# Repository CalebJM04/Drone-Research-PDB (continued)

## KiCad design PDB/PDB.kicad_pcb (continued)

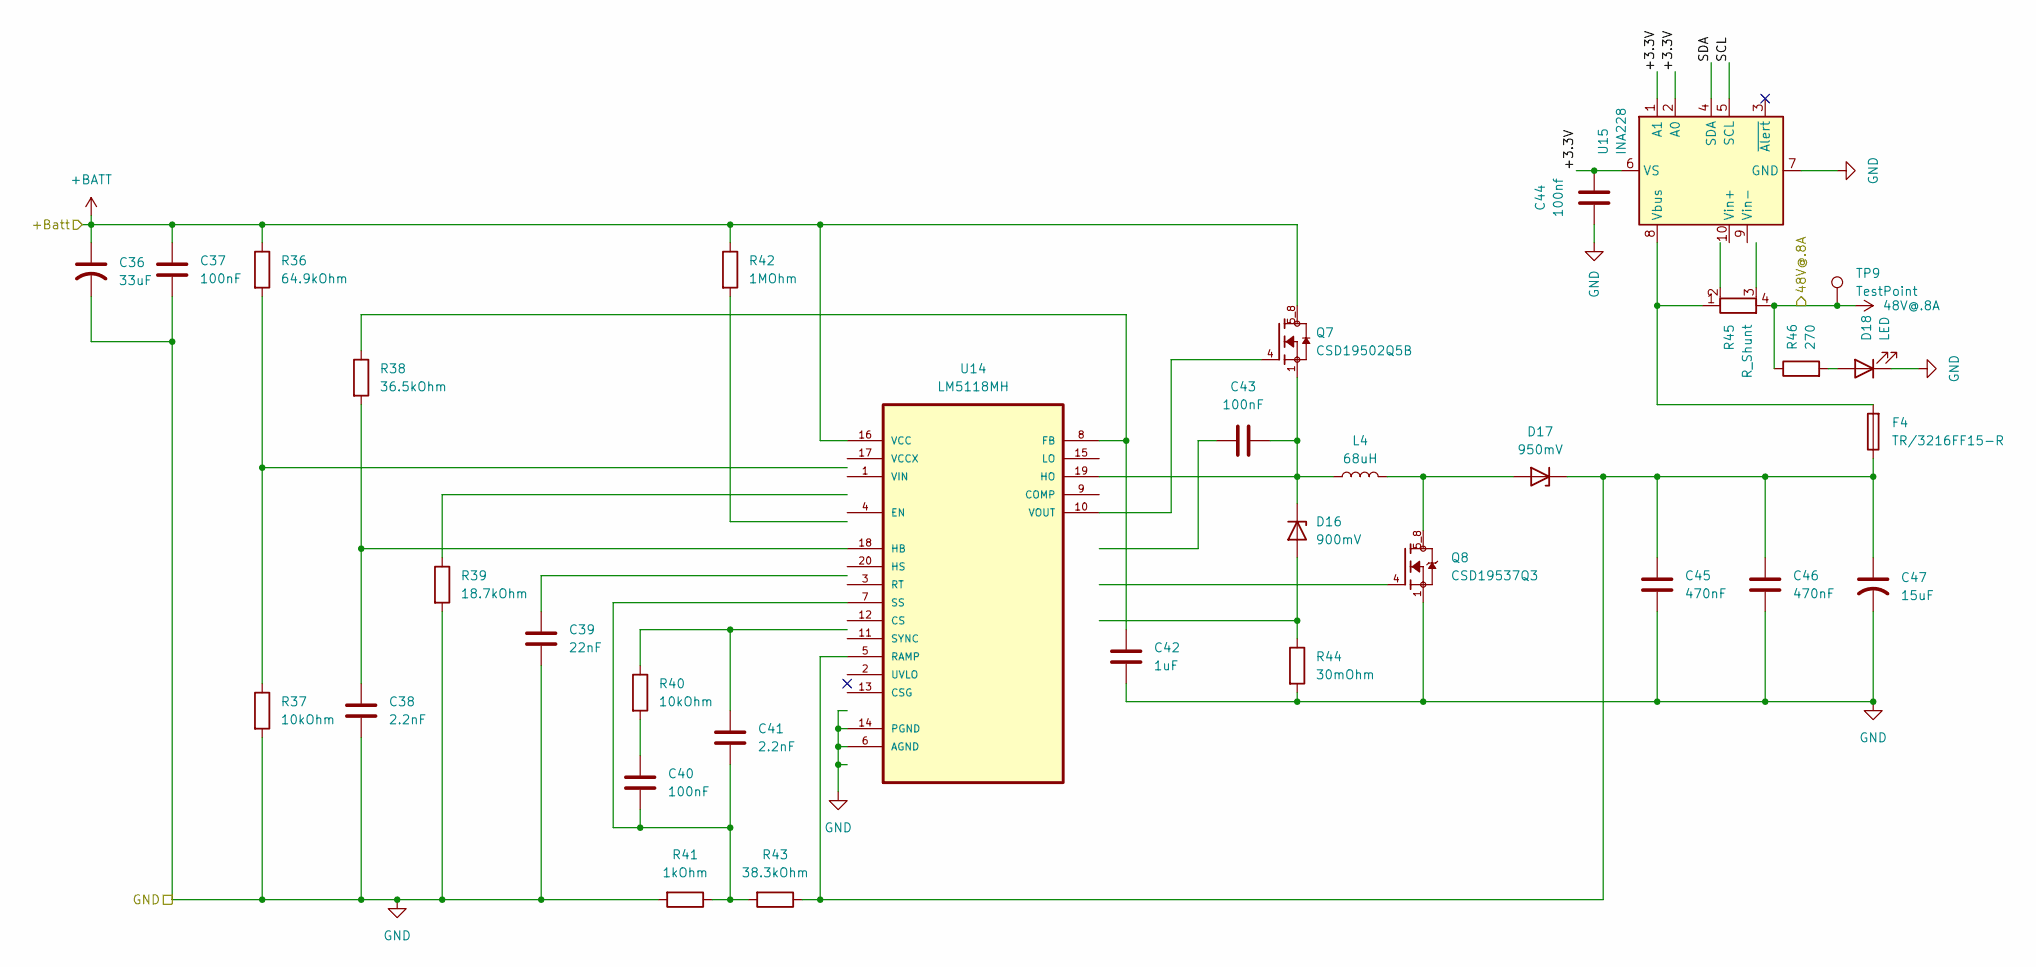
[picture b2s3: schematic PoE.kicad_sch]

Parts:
C36: 33uF; C_0603_1608Metric
C37, C40, C43: 100nF; C_0603_1608Metric
C38, C41: 2.2nF; C_0603_1608Metric
C39: 22nF; C_0603_1608Metric
C42: 1uF; C_0603_1608Metric
C44: 100nf; C_0603_1608Metric
C45, C46: 470nF; C_0603_1608Metric
C47: 15uF; C_0603_1608Metric
D16: 900mV; D_SOD-523
D17: 950mV; D_SOD-523
D18: LED; LED_0805_2012Metric
F4: TR/3216FF15-R; Fuse_1206_3216Metric
L4: 68uH; L_1206_3216Metric
Q7: CSD19502Q5B; TRANS_CSD19502Q5B; PARTREV May 2017; DigiKey_Part_Number 296-37194-1-ND
Q8: CSD19537Q3; TRANS_CSD19537Q3; PARTREV A; DigiKey_Part_Number 296-44351-1-ND
R36: 64.9kOhm; R_0603_1608Metric
R37, R40: 10kOhm; R_0603_1608Metric
R38: 36.5kOhm; R_0603_1608Metric
R39: 18.7kOhm; R_0603_1608Metric
R41: 1kOhm; R_0603_1608Metric
R42: 1MOhm; R_0603_1608Metric
R43: 38.3kOhm; R_0603_1608Metric
R44: 30mOhm; R_0603_1608Metric
R45: R_Shunt; R_Shunt_Vishay_WSK2512_6332Metric_T2.66mm
R46: 270; R_1206_3216Metric_Pad1.30x1.75mm_HandSolder
TP9: TestPoint; TestPoint_Pad_D2.0mm
U14: LM5118MH; SOP65P640X110-21N; MPN LM5118MH; DigiKey_Part_Number LM5118MH/NOPB-ND
U15: INA228; TSSOP-10_3x3mm_P0.5mm

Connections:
48V@.8A: R45.4, R46.1, TP9.1 (1_1)
+BATT: C36.1, C37.1, Q7.5_8, R36.1, R42.1, U14.16 (VCC); also elsewhere on the board
/48V@.8A/+3.3V: C44.2, U15.1 (A1), U15.2 (A0), U15.6 (VS)
/48V@.8A/SCL: U15.5 (SCL)
/48V@.8A/SDA: U15.4 (SDA)
GND: C36.2, C37.2, C38.2, C39.2, C42.2, C44.1, C45.2, C46.2, C47.2, D18.1 (K), Q8.1, Q8.2, Q8.3, R37.2, R39.2, R41.2, R44.2, U14.6 (AGND), U14.14 (PGND), U15.7 (GND); also elsewhere on the board
unnamed: C40.1, R40.2
unnamed: C41.1, R40.1
unnamed: D16.2 (A), R44.1
unnamed: C43.1, D16.1 (K), L4.1, Q7.1, Q7.2, Q7.3, U14.19 (HO)
unnamed: D17.2 (A), L4.2, Q8.5_8
unnamed: C45.1, C46.1, C47.1, D17.1 (K), F4.1, R43.1, U14.5 (RAMP)
unnamed: D18.2 (A), R46.2
unnamed: R36.2, R37.1
unnamed: C42.1, R38.1, U14.8 (FB)
unnamed: C38.1, R38.2, U14.18 (HB)
unnamed: C40.2, C41.2, R41.1, R43.2, U14.7 (SS)
unnamed: Q7.4, U14.10 (VOUT)
unnamed: F4.2, R45.1, U15.8 (Vbus)

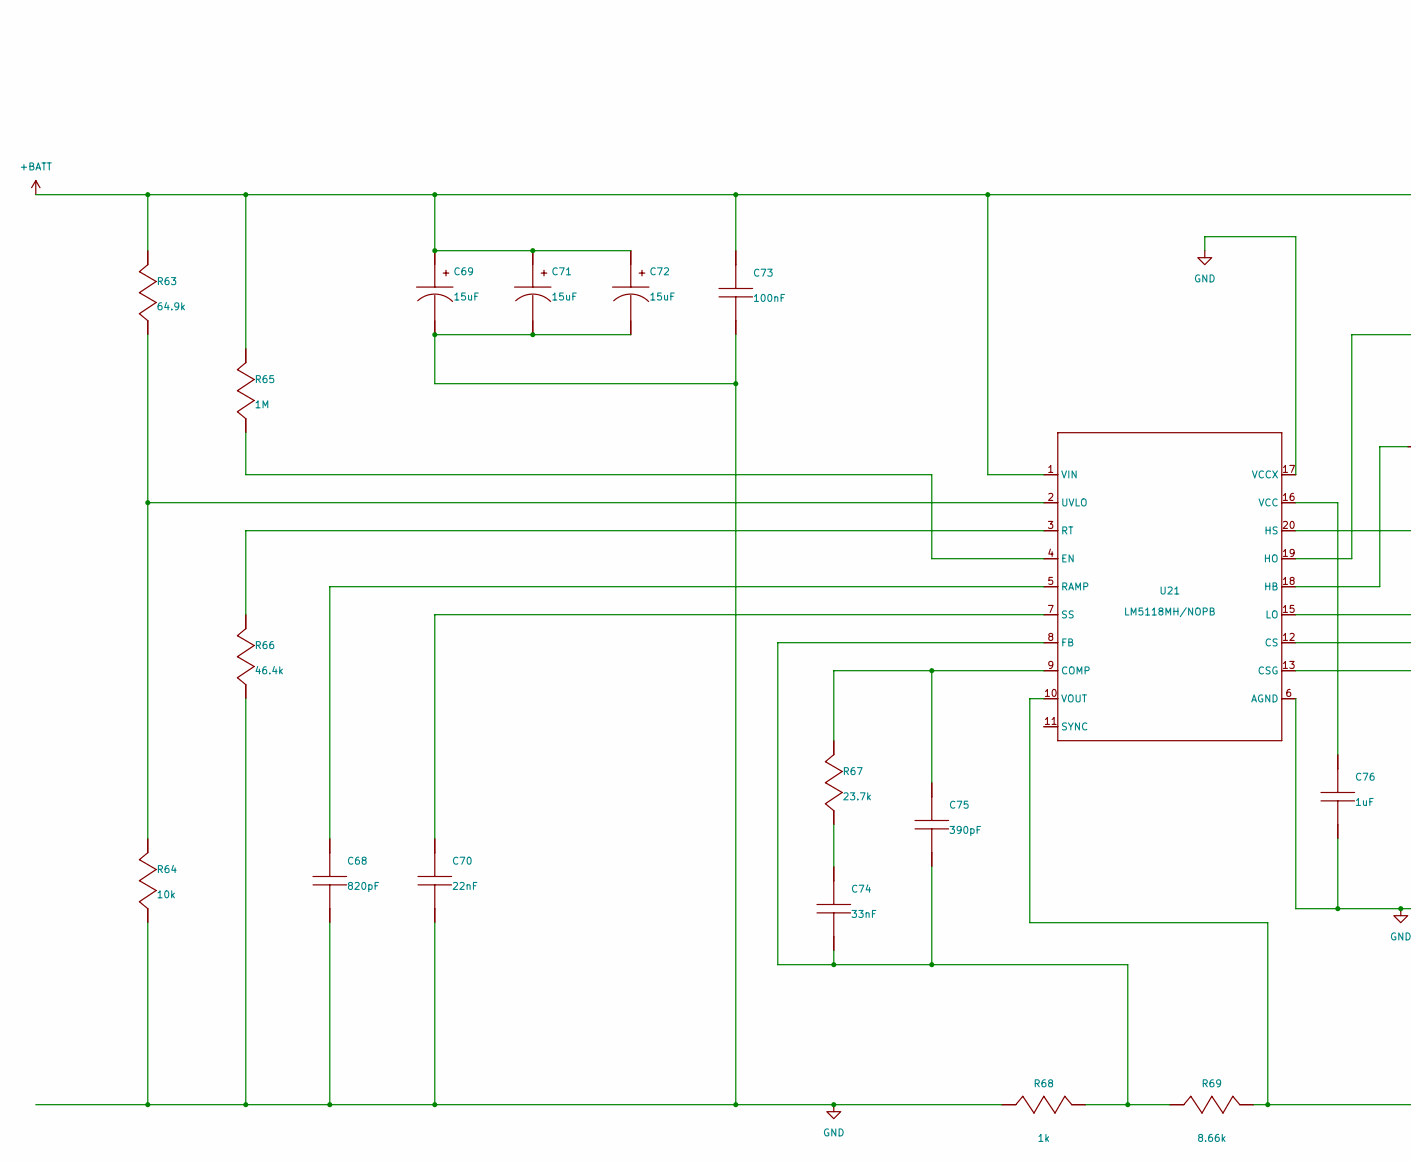
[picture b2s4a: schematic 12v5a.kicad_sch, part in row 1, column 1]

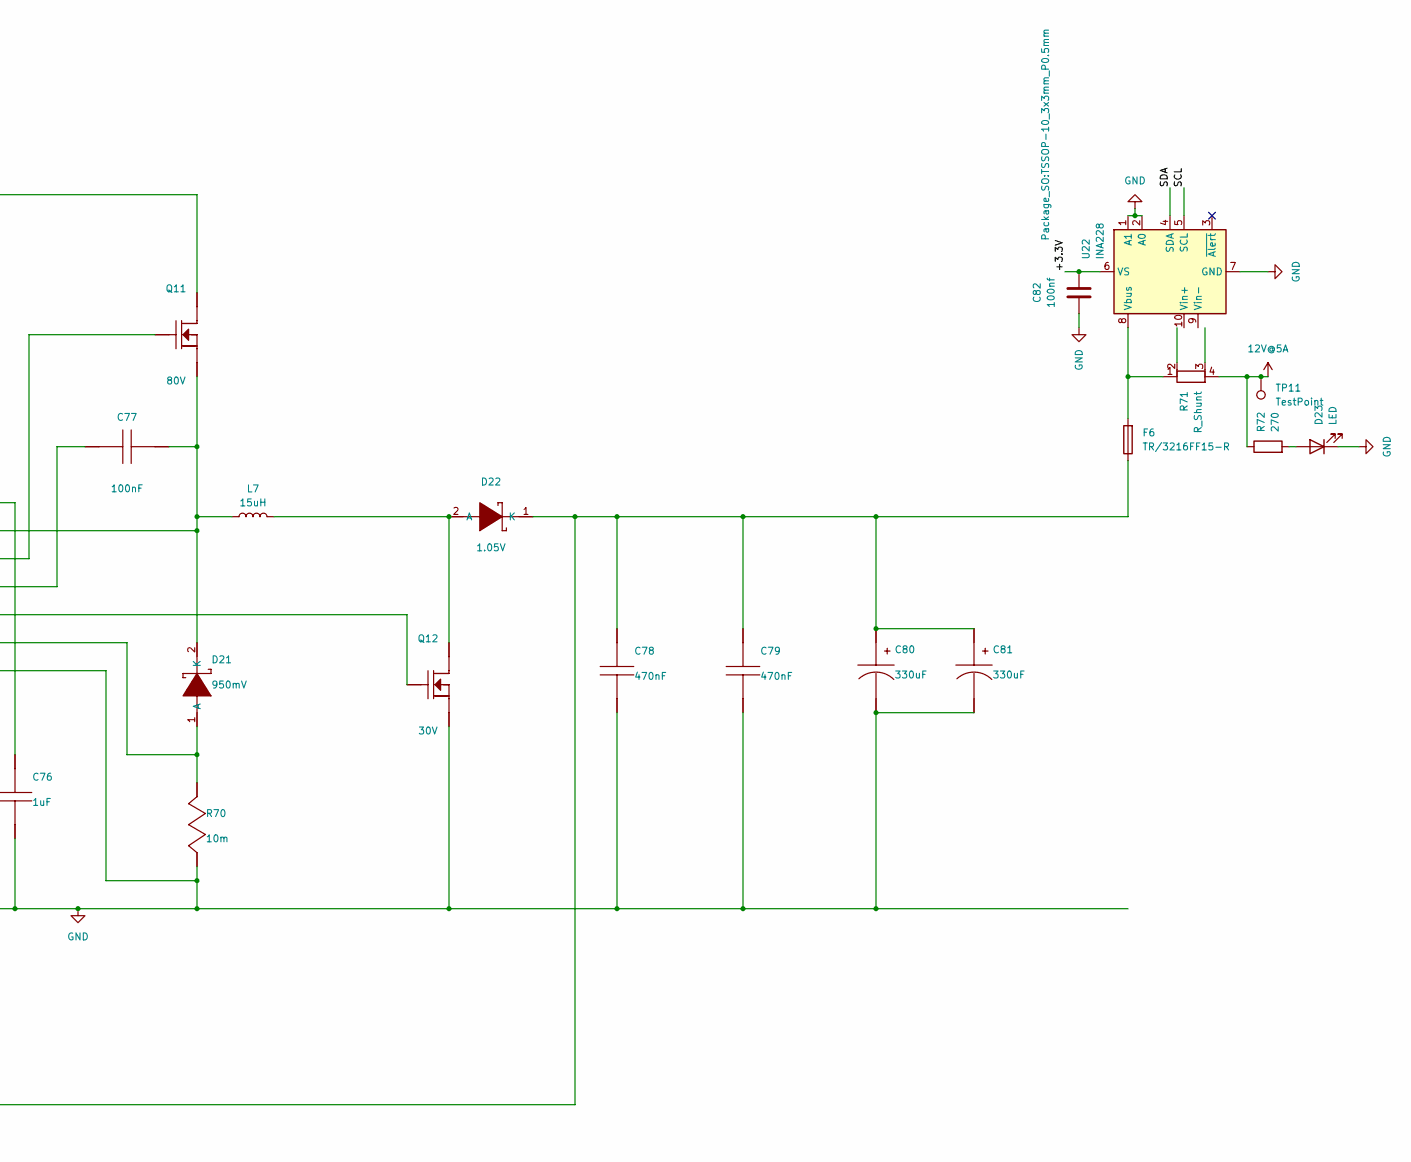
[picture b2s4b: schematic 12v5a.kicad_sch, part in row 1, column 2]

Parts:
C68: CL05C821JB5NNNC; C_0603_1608Metric; MANUFACTURER PART NUMBER CL05C821JB5NNNC
C69, C71, C72: 100SXV15M; C_0603_1608Metric; MANUFACTURER PART NUMBER 100SXV15M
C70: C2012C0G1H223K125AA; C_0603_1608Metric; MANUFACTURER PART NUMBER C2012C0G1H223K125AA
C73: C2012X7R2A104K125AA; C_0603_1608Metric; MANUFACTURER PART NUMBER C2012X7R2A104K125AA
C74: CGA4J2C0G1H333J125AA; C_0603_1608Metric; MANUFACTURER PART NUMBER CGA4J2C0G1H333J125AA
C75: GRM1555C1H391JA01J; C_0603_1608Metric; MANUFACTURER PART NUMBER GRM1555C1H391JA01J
C76: C1005X5R1E105K050BC; C_0603_1608Metric; MANUFACTURER PART NUMBER C1005X5R1E105K050BC
C77: 08053C104JAZ2A; C_0603_1608Metric; MANUFACTURER PART NUMBER 08053C104JAZ2A
C78, C79: C1005X6S1C474K050BC; C_0603_1608Metric; MANUFACTURER PART NUMBER C1005X6S1C474K050BC
C80, C81: EEHZC1E331P; C_0603_1608Metric; MANUFACTURER PART NUMBER EEHZC1E331P
C82: 100nf; C_0603_1608Metric
D21: SBRD10200TR; TO-252-2_TabPin1; MANUFACTURER PART NUMBER SBRD10200TR
D22: SB20150TR; D_5W_P10.16mm_Horizontal; MANUFACTURER PART NUMBER SB20150TR
D23: LED; LED_0805_2012Metric
F6: TR/3216FF15-R; Fuse_1206_3216Metric
L7: 15uH; L_1206_3216Metric
Q11: CSD19502Q5B; MANUFACTURER PART NUMBER CSD19502Q5B
Q12: CSD17578Q3A; CSD19502Q5B; MANUFACTURER PART NUMBER CSD17578Q3A
R63: CRCW040264K9FKED; R_0603_1608Metric; MANUFACTURER PART NUMBER CRCW040264K9FKED
R64: RC0201FR-0710KL; R_0603_1608Metric; MANUFACTURER PART NUMBER RC0201FR-0710KL
R65: CRCW04021M00FKED; R_0603_1608Metric; MANUFACTURER PART NUMBER CRCW04021M00FKED
R66: CRCW040246K4FKED; R_0603_1608Metric; MANUFACTURER PART NUMBER CRCW040246K4FKED
R67: RC0201FR-0723K7L; R_0603_1608Metric; MANUFACTURER PART NUMBER RC0201FR-0723K7L
R68: CRCW04021K00FKED; R_0603_1608Metric; MANUFACTURER PART NUMBER CRCW04021K00FKED
R69: CRCW04028K66FKED; R_0603_1608Metric; MANUFACTURER PART NUMBER CRCW04028K66FKED
R70: CRA2512-FZ-R010ELF; R_0603_1608Metric; MANUFACTURER PART NUMBER CRA2512-FZ-R010ELF
R71: R_Shunt; R_Shunt_Vishay_WSK2512_6332Metric_T2.21mm
R72: 270; C_0603_1608Metric
TP11: TestPoint; TestPoint_Pad_D2.0mm
U21: LM5118MH/NOPB; LM5118MH; MANUFACTURER PART NUMBER LM5118MH/NOPB
U22: INA228; TSSOP-10_3x3mm_P0.5mm

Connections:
12V@5A: R71.4, R72.1, TP11.1 (1_1)
+BATT: C69.1 (+), C71.1 (+), C72.1 (+), C73.1, Q11.1 (Drain), Q11.2 (Drain), Q11.5 (Drain), Q11.6 (Drain), Q11.8 (Drain), R63.1, R65.1, U21.1 (VIN); also elsewhere on the board
/12v5a/+3.3V: C82.2, U22.6 (VS)
/12v5a/SCL: U22.5 (SCL)
/12v5a/SDA: U22.4 (SDA)
GND: C68.2, C69.2 (-), C70.2, C71.2 (-), C72.2 (-), C73.2, C76.2, C78.2, C79.2, C80.2 (-), C81.2 (-), C82.1, D23.1 (K), Q12.1 (Source), Q12.2 (Source), Q12.3 (Source), R64.2, R66.2, R68.2, R70.2, U21.6 (AGND), U21.13 (CSG), U21.14 (PGND), U21.17 (VCCX), U21.21 (EP), U22.1 (A1), U22.2 (A0), U22.7 (GND); also elsewhere on the board
unnamed: C74.1, R67.2
unnamed: C78.1, C79.1, C80.1 (+), C81.1 (+), D22.1 (K), F6.1, R69.1, U21.10 (VOUT)
unnamed: C77.1, D21.2 (K), L7.1, Q11.4 (Source), Q11.7 (Source), U21.20 (HS)
unnamed: D22.2 (A), L7.2, Q12.5 (Drain), Q12.6 (Drain), Q12.7 (Drain), Q12.8 (Drain), Q12.9 (Drain)
unnamed: D23.2 (A), R72.2
unnamed: Q11.3 (Gate), U21.19 (HO)
unnamed: Q12.4 (Gate), U21.15 (LO)
unnamed: C75.1, R67.1, U21.9 (COMP)
unnamed: D21.1 (A), D21.3 (A), R70.1, U21.12 (CS)
unnamed: R65.2, U21.4 (EN)
unnamed: C74.2, C75.2, R68.1, R69.2, U21.8 (FB)
unnamed: C77.2, U21.18 (HB)
unnamed: C68.1, U21.5 (RAMP)
unnamed: R66.1, U21.3 (RT)
unnamed: C70.1, U21.7 (SS)
unnamed: R63.2, R64.1, U21.2 (UVLO)
unnamed: C76.1, U21.16 (VCC)
unnamed: F6.2, R71.1, U22.8 (Vbus)

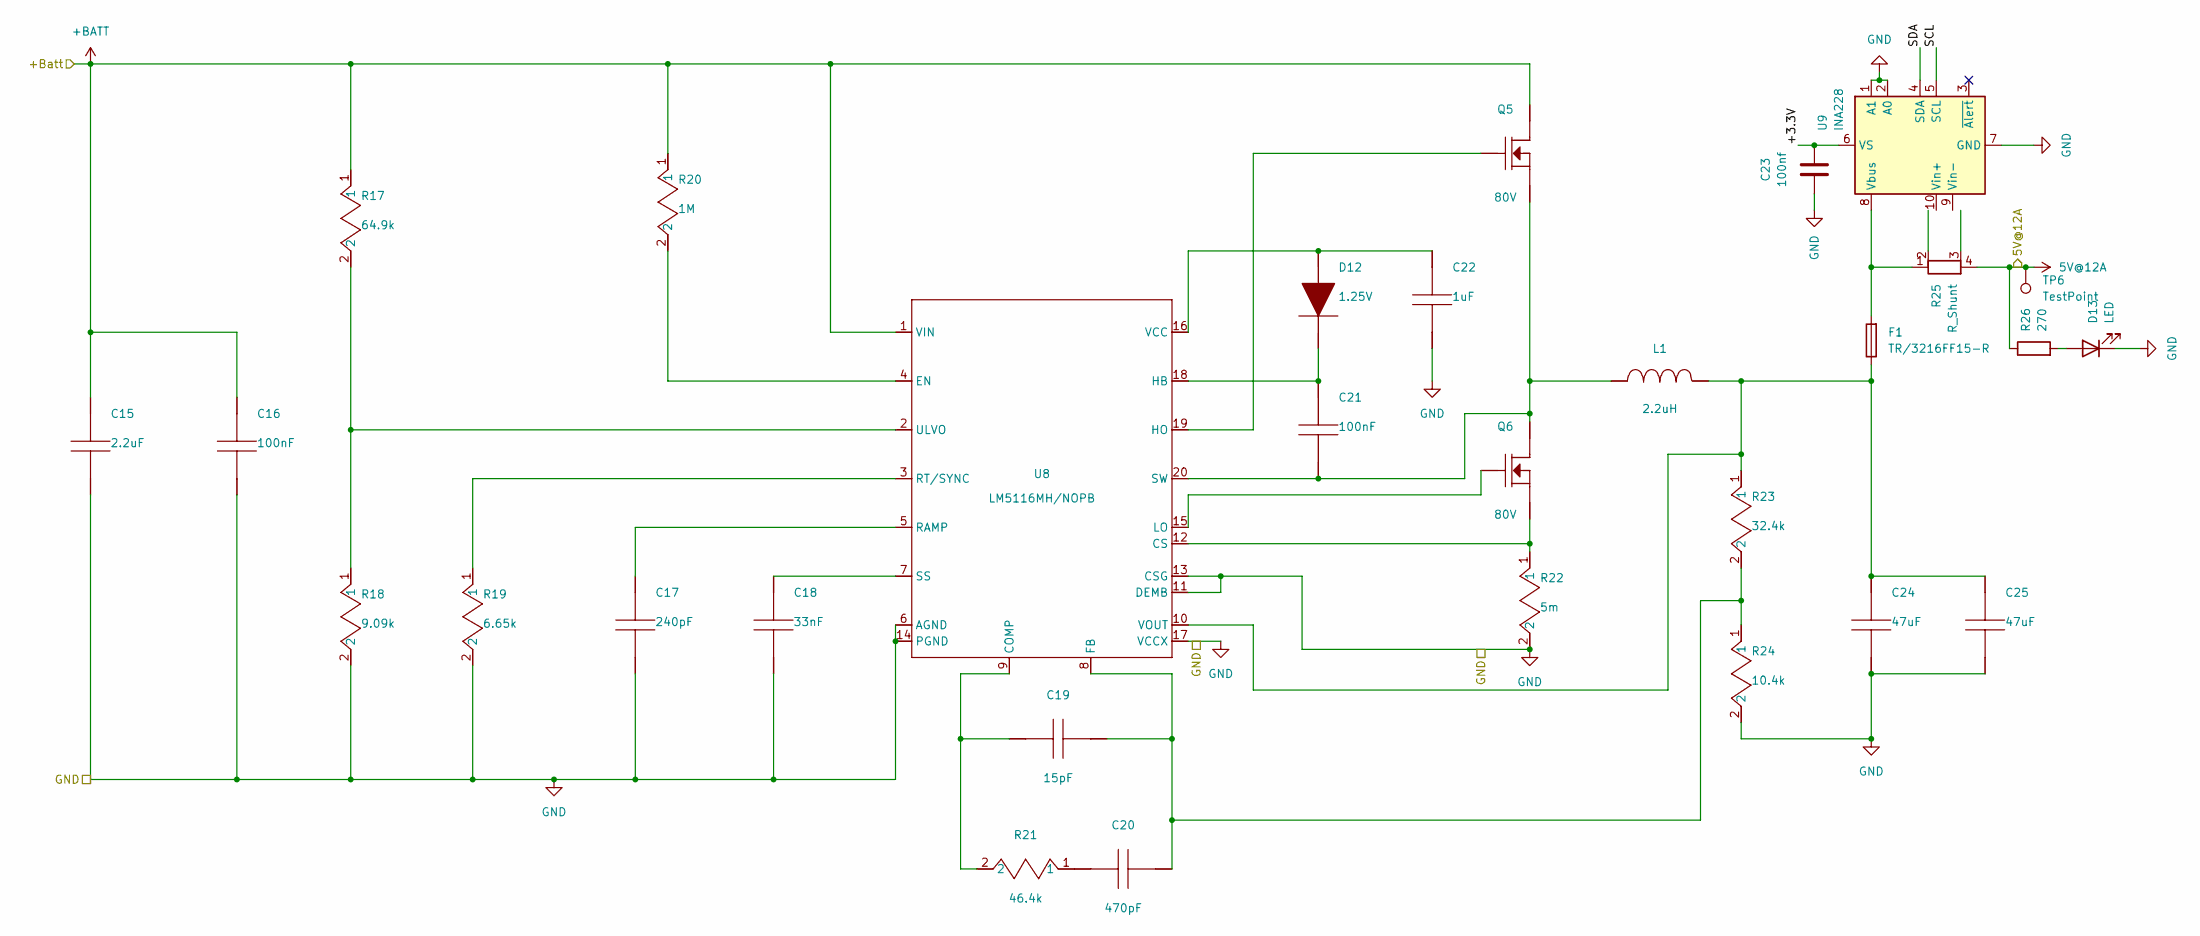
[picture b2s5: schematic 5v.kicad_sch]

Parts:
C15: C3225X7R2A225K230AB; C_0603_1608Metric; MANUFACTURER PART NUMBER C3225X7R2A225K230AB
C16: C2012X7R2A104K125AA; C_0603_1608Metric; MANUFACTURER PART NUMBER C2012X7R2A104K125AA
C17: GRM1555C1H241GA01D; C_0603_1608Metric; MANUFACTURER PART NUMBER GRM1555C1H241GA01D
C18: CGA4J2C0G1H333J125AA; C_0603_1608Metric; MANUFACTURER PART NUMBER CGA4J2C0G1H333J125AA
C19: C0402C150J4GACTU; C_0603_1608Metric; MANUFACTURER PART NUMBER C0402C150J4GACTU
C20: 04025A471JAT2A; C_0603_1608Metric; MANUFACTURER PART NUMBER 04025A471JAT2A
C21: 08053C104KAT2A; C_0603_1608Metric; MANUFACTURER PART NUMBER 08053C104KAT2A
C22: C1005X5R1E105K050BC; C_0603_1608Metric; MANUFACTURER PART NUMBER C1005X5R1E105K050BC
C23: 100nf; C_0603_1608Metric
C24, C25: GRM32ER61C476KE15L; C_0603_1608Metric; MANUFACTURER PART NUMBER GRM32ER61C476KE15L
D12: BAS516,115; D_SOD-523; MANUFACTURER PART NUMBER BAS516,115
D13: LED; LED_0805_2012Metric
F1: TR/3216FF15-R; Fuse_1206_3216Metric
L1: XAL7070-222MEB; L_1206_3216Metric; MANUFACTURER PART NUMBER XAL7070-222MEB
Q5, Q6: GENERIC_MOSFET_N; Infineon_PG-TDSON-8_6.15x5.15mm; MANUFACTURER PART NUMBER GENERIC_MOSFET_N
R17: CRCW080564K9FKEA; R_0603_1608Metric; MANUFACTURER PART NUMBER CRCW080564K9FKEA
R18: ERJ-6ENF9091V; R_0603_1608Metric; MANUFACTURER PART NUMBER ERJ-6ENF9091V
R19: CRCW04026K65FKED; R_0603_1608Metric; MANUFACTURER PART NUMBER CRCW04026K65FKED
R20: CRCW04021M00FKED; R_0603_1608Metric; MANUFACTURER PART NUMBER CRCW04021M00FKED
R21: CRCW040246K4FKED; R_0603_1608Metric; MANUFACTURER PART NUMBER CRCW040246K4FKED
R22: PRL1632-R005-F-T1; R_0603_1608Metric; MANUFACTURER PART NUMBER PRL1632-R005-F-T1
R23: ERJ-6ENF3242V; R_0603_1608Metric; MANUFACTURER PART NUMBER ERJ-6ENF3242V
R24: RT0805BRD0710K4L; R_0603_1608Metric; MANUFACTURER PART NUMBER RT0805BRD0710K4L
R25: R_Shunt; R_Shunt_Vishay_WSK2512_6332Metric_T2.66mm
R26: 270; R_1206_3216Metric_Pad1.30x1.75mm_HandSolder
TP6: TestPoint; TestPoint_Pad_D2.0mm
U8: LM5116MH/NOPB; MXA20A_TEX; MANUFACTURER PART NUMBER LM5116MH/NOPB
U9: INA228; TSSOP-10_3x3mm_P0.5mm

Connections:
5V@12A: R25.4, R26.1, TP6.1 (1_1); also elsewhere on the board
+BATT: C15.1, C16.1, Q5.2 (Drain), R17.1, R20.1, U8.1 (VIN); also elsewhere on the board
/5V@12A/+3.3V: C23.2, U9.6 (VS)
/5V@12A/SCL: U9.5 (SCL)
/5V@12A/SDA: U9.4 (SDA)
GND: C15.2, C16.2, C17.2, C18.2, C22.2, C23.1, C24.2, C25.2, D13.1 (K), R18.2, R19.2, R22.2, R24.2, U8.6 (AGND), U8.11 (DEMB), U8.13 (CSG), U8.14 (PGND), U8.17 (VCCX), U8.21 (EP), U9.1 (A1), U9.2 (A0), U9.7 (GND); also elsewhere on the board
unnamed: C20.2, R21.1
unnamed: C22.1, D12.2 (A), U8.16 (VCC)
unnamed: C21.1, D12.1 (K), U8.18 (HB)
unnamed: D13.2 (A), R26.2
unnamed: Q5.1 (Gate), U8.19 (HO)
unnamed: C21.2, L1.1, Q5.3 (Source), Q6.2 (Drain), U8.20 (SW)
unnamed: Q6.1 (Gate), U8.15 (LO)
unnamed: Q6.3 (Source), R22.1, U8.12 (CS)
unnamed: C19.1, R21.2, U8.9 (COMP)
unnamed: R20.2, U8.4 (EN)
unnamed: C19.2, C20.1, R23.2, R24.1, U8.8 (FB)
unnamed: C17.1, U8.5 (RAMP)
unnamed: R19.1, U8.3 (RT/SYNC)
unnamed: C18.1, U8.7 (SS)
unnamed: R17.2, R18.1, U8.2 (ULVO)
unnamed: C24.1, C25.1, F1.1, L1.2, R23.1, U8.10 (VOUT)
unnamed: F1.2, R25.1, U9.8 (Vbus)

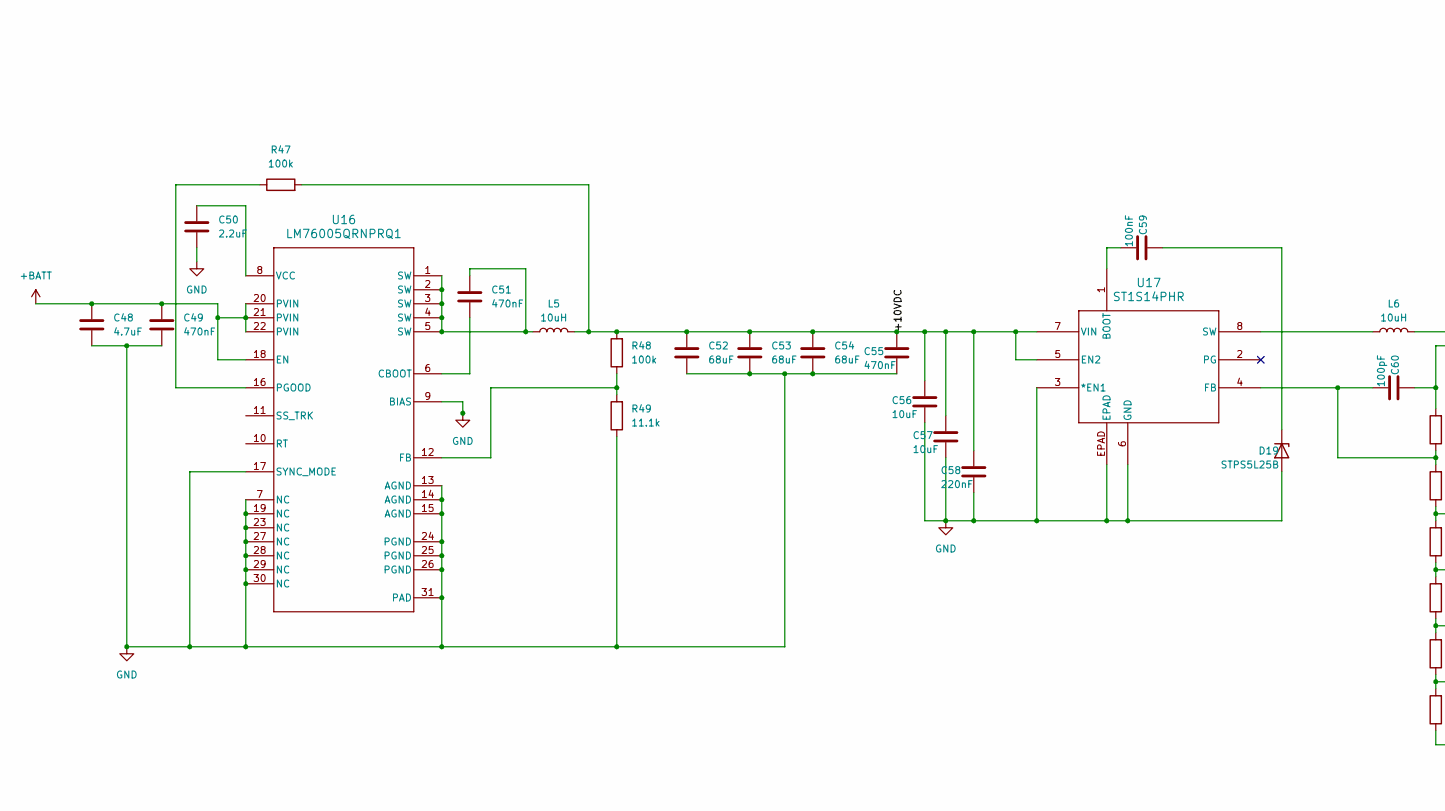
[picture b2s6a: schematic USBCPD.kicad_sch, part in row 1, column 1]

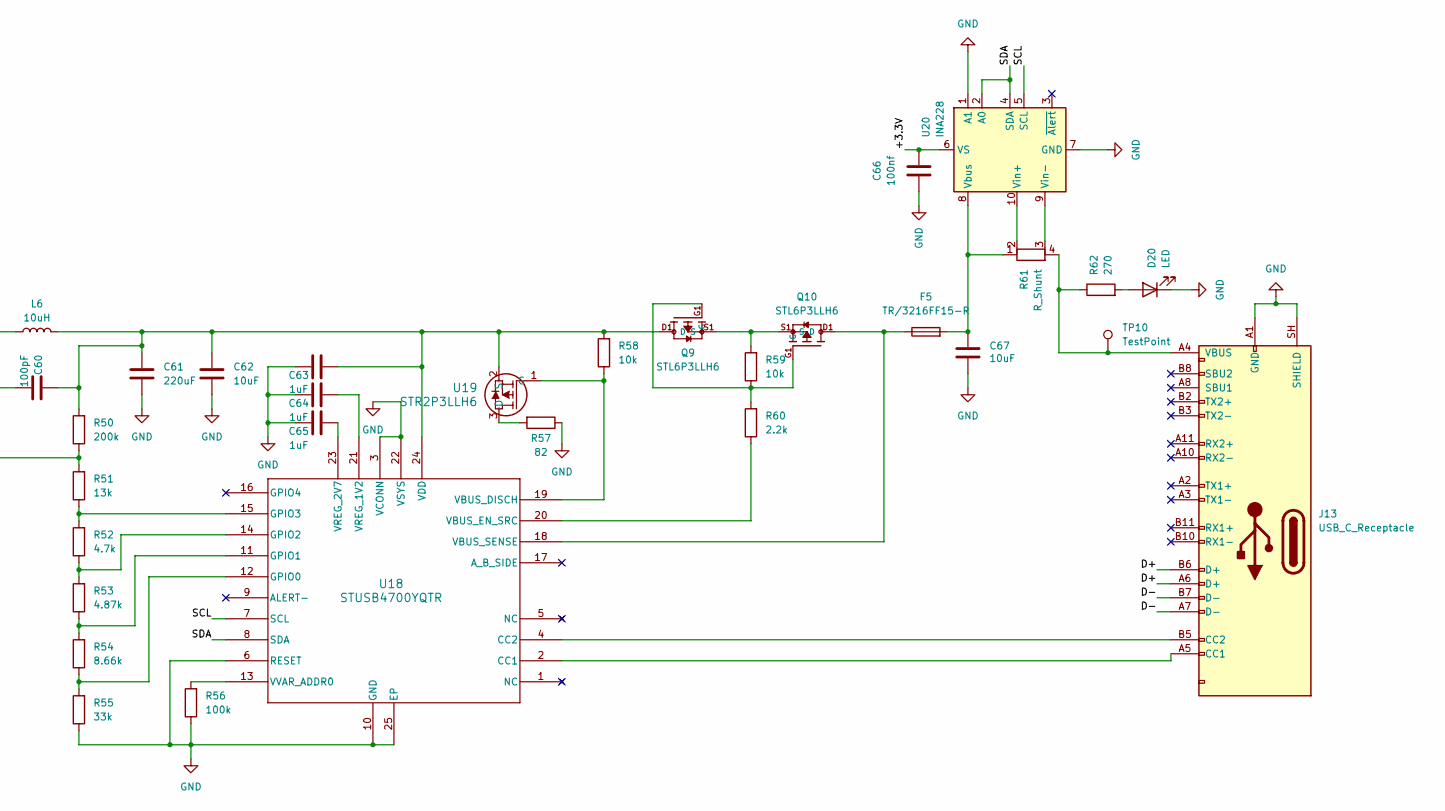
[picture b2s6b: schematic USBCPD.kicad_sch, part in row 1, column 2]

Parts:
C48: 4.7uF; C_0603_1608Metric_Pad1.08x0.95mm_HandSolder
C49, C51, C55: 470nF; C_0603_1608Metric_Pad1.08x0.95mm_HandSolder
C50: 2.2uF; C_0603_1608Metric_Pad1.08x0.95mm_HandSolder
C52, C53, C54: 68uF; C_0603_1608Metric_Pad1.08x0.95mm_HandSolder
C56, C57, C62, C67: 10uF; C_0603_1608Metric_Pad1.08x0.95mm_HandSolder
C58: 220nF; C_0603_1608Metric_Pad1.08x0.95mm_HandSolder
C59: 100nF; C_0603_1608Metric_Pad1.08x0.95mm_HandSolder
C60: 100pF; C_0603_1608Metric_Pad1.08x0.95mm_HandSolder
C61: 220uF; C_0603_1608Metric_Pad1.08x0.95mm_HandSolder
C63, C64, C65: 1uF; C_0603_1608Metric_Pad1.08x0.95mm_HandSolder
C66: 100nf; C_0603_1608Metric
D19: STPS5L25B; TO-252-2
D20: LED; LED_0805_2012Metric
F5: TR/3216FF15-R; Fuse_1206_3216Metric
J13: USB_C_Receptacle; USB_C_Receptacle_CNCTech_C-ARA1-AK51X
L5, L6: 10uH; L_1206_3216Metric
Q9, Q10: STL6P3LLH6; TRANS_STL6P3LLH6; PARTREV 4
R47, R48, R56: 100k; R_0603_1608Metric_Pad0.98x0.95mm_HandSolder
R49: 11.1k; R_0603_1608Metric_Pad0.98x0.95mm_HandSolder
R50: 200k; R_0603_1608Metric_Pad0.98x0.95mm_HandSolder
R51: 13k; R_0603_1608Metric_Pad0.98x0.95mm_HandSolder
R52: 4.7k; R_0603_1608Metric_Pad0.98x0.95mm_HandSolder
R53: 4.87k; R_0603_1608Metric_Pad0.98x0.95mm_HandSolder
R54: 8.66k; R_0603_1608Metric_Pad0.98x0.95mm_HandSolder
R55: 33k; R_0603_1608Metric_Pad0.98x0.95mm_HandSolder
R57: 82; R_0603_1608Metric_Pad0.98x0.95mm_HandSolder
R58, R59: 10k; R_0603_1608Metric_Pad0.98x0.95mm_HandSolder
R60: 2.2k; R_0603_1608Metric_Pad0.98x0.95mm_HandSolder
R61: R_Shunt; R_Shunt_Vishay_WSK2512_6332Metric_T2.66mm
R62: 270; R_1206_3216Metric_Pad1.30x1.75mm_HandSolder
TP10: TestPoint; TestPoint_Pad_D2.0mm
U16: LM76005QRNPRQ1; LM76005RNPR
U17: ST1S14PHR; HSOP8_STM
U18: STUSB4700YQTR; QFN_700QTR_STM
U19: STR2P3LLH6; SOT_3LLH6_STM
U20: INA228; HVSSOP-10-1EP_3x3mm_P0.5mm_EP1.83x1.89mm

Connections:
+BATT: C48.1, C49.1, U16.18 (EN), U16.20 (PVIN), U16.21 (PVIN), U16.22 (PVIN); also elsewhere on the board
/USB-C PD/+3.3V: C66.2, U20.6 (VS)
/USB-C PD/+10VDC: C52.1, C53.1, C54.1, C55.1, C56.1, C57.1, C58.1, L5.2, R47.2, R48.2, U17.5 (EN2), U17.7 (VIN)
/USB-C PD/D+: J13.A6 (D+), J13.B6 (D+)
/USB-C PD/D-: J13.A7 (D-), J13.B7 (D-)
/USB-C PD/SCL: U18.7 (SCL), U20.5 (SCL)
/USB-C PD/SDA: U18.8 (SDA), U20.2 (A0), U20.4 (SDA)
GND: C48.2, C49.2, C50.2, C52.2, C53.2, C54.2, C55.2, C56.2, C57.2, C58.2, C61.2, C62.2, C63.1, C64.1, C65.1, C66.1, C67.2, D19.2 (A), D20.1 (K), J13.A1 (GND), J13.A12 (GND), J13.B1 (GND), J13.B12 (GND), J13.SH (SHIELD), R49.1, R55.1, R56.1, R57.1, U16.7 (NC), U16.9 (BIAS), U16.13 (AGND), U16.14 (AGND), U16.15 (AGND), U16.17 (SYNC_MODE), U16.19 (NC), U16.23 (NC), U16.24 (PGND), U16.25 (PGND), U16.26 (PGND), U16.27 (NC), U16.28 (NC), U16.29 (NC), U16.30 (NC), U16.31 (PAD), U16.36, U16.38, U16.39, U16.40, U16.41, U17.3 (*EN1), U17.6 (GND), U17.EPAD, U18.3 (VCONN), U18.6 (RESET), U18.10 (GND), U18.22 (VSYS), U18.25 (EP), U20.1 (A1), U20.7 (GND); also elsewhere on the board
unnamed: C51.1, L5.1, U16.1 (SW), U16.2 (SW), U16.3 (SW), U16.4 (SW), U16.5 (SW)
unnamed: C59.1, D19.1 (K)
unnamed: D20.2 (A), R62.2
unnamed: J13.A5 (CC1), U18.2 (CC1)
unnamed: J13.B5 (CC2), U18.4 (CC2)
unnamed: J13.A4 (VBUS), R61.4, R62.1, TP10.1 (1_1)
unnamed: J13.A9 (VBUS), J13.B4 (VBUS), J13.B9 (VBUS)
unnamed: C60.1, C61.1, C62.1, C63.2, L6.2, Q9.D1 (D), R50.2, R58.2, U18.24 (VDD), U19.2 (S)
unnamed: F5.1, Q10.D1 (D), U18.18 (VBUS_SENSE)
unnamed: Q9.G1 (G), Q10.G1 (G), R59.1, R60.2
unnamed: Q9.S1 (S), Q10.S1 (S), R59.2
unnamed: C51.2, U16.6 (CBOOT)
unnamed: R48.1, R49.2, U16.12 (FB)
unnamed: R47.1, U16.16 (PGOOD)
unnamed: C50.1, U16.8 (VCC)
unnamed: C59.2, U17.1 (BOOT)
unnamed: C60.2, R50.1, R51.2, U17.4 (FB)
unnamed: L6.1, U17.8 (SW)
unnamed: R54.1, R55.2, U18.12 (GPIO0)
unnamed: R53.1, R54.2, U18.11 (GPIO1)
unnamed: R52.1, R53.2, U18.14 (GPIO2)
unnamed: R51.1, R52.2, U18.15 (GPIO3)
unnamed: R58.1, U18.19 (VBUS_DISCH), U19.1 (G)
unnamed: R60.1, U18.20 (VBUS_EN_SRC)
unnamed: C64.2, U18.21 (VREG_1V2)
unnamed: C65.2, U18.23 (VREG_2V7)
unnamed: R56.2, U18.13 (VVAR_ADDR0)
unnamed: R57.2, U19.3 (D)
unnamed: C67.1, F5.2, R61.1, U20.8 (Vbus)
unnamed: R61.2, U20.10 (Vin+)
unnamed: R61.3, U20.9 (Vin-)

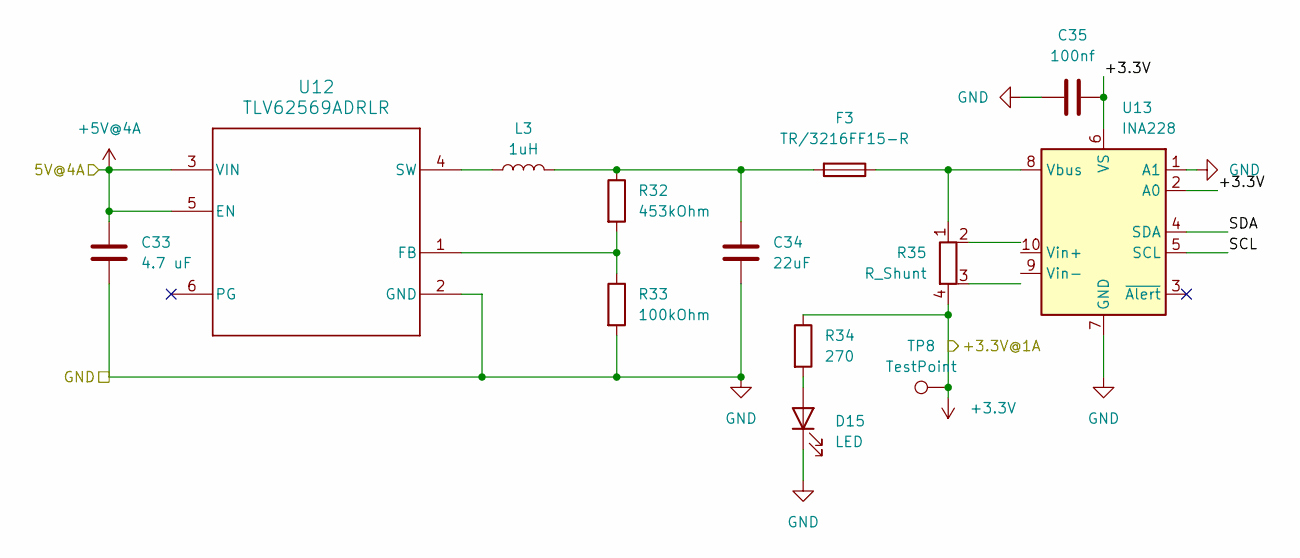
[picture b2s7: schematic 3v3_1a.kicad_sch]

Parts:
C33: 4.7 uF; C_0603_1608Metric
C34: 22uF; C_0603_1608Metric
C35: 100nf; C_0603_1608Metric
D15: LED; LED_0805_2012Metric
F3: TR/3216FF15-R; Fuse_1206_3216Metric
L3: 1uH; L_1206_3216Metric
R32: 453kOhm; R_0603_1608Metric
R33: 100kOhm; R_0603_1608Metric
R34: 270; R_0603_1608Metric
R35: R_Shunt; R_Shunt_Vishay_WSK2512_6332Metric_T2.66mm
TP8: TestPoint; TestPoint_Pad_D2.0mm
U12: TLV62569ADRLR; DRL0006A
U13: INA228; TSSOP-10_3x3mm_P0.5mm

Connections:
+3.3V: C35.2, R34.1, R35.4, TP8.1 (1_1), U13.2 (A0), U13.6 (VS); also elsewhere on the board
+5V@4A: C33.1, U12.3 (VIN), U12.5 (EN); also elsewhere on the board
/3V3@1A/SCL: U13.5 (SCL)
/3V3@1A/SDA: U13.4 (SDA)
GND: C33.2, C34.2, C35.1, D15.1 (K), R33.2, U12.2 (GND), U13.1 (A1), U13.7 (GND); also elsewhere on the board
unnamed: C34.1, F3.2, L3.2, R32.1
unnamed: D15.2 (A), R34.2
unnamed: R32.2, R33.1, U12.1 (FB)
unnamed: L3.1, U12.4 (SW)
unnamed: F3.1, R35.1, U13.8 (Vbus)

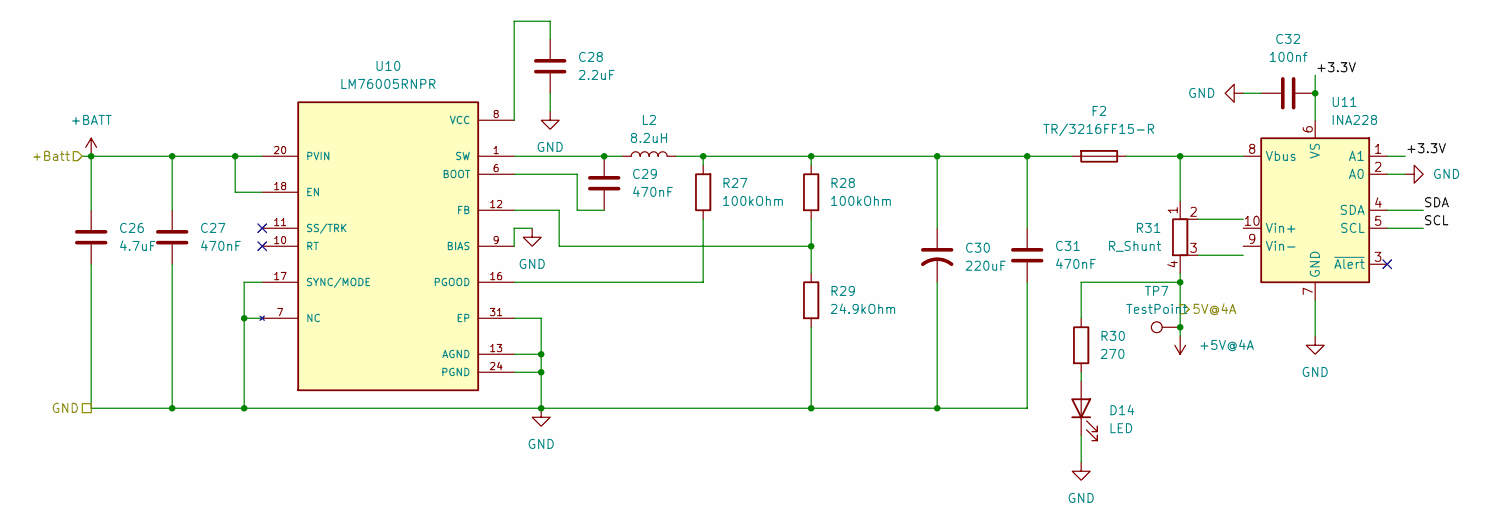
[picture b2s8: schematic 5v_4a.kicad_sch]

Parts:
C26: 4.7uF; C_0603_1608Metric
C27, C29, C31: 470nF; C_0603_1608Metric
C28: 2.2uF; C_0603_1608Metric
C30: 220uF; C_0603_1608Metric
C32: 100nf; C_0603_1608Metric
D14: LED; LED_0805_2012Metric
F2: TR/3216FF15-R; Fuse_1206_3216Metric
L2: 8.2uH; L_1206_3216Metric
R27, R28: 100kOhm; R_0603_1608Metric
R29: 24.9kOhm; R_0603_1608Metric
R30: 270; R_0603_1608Metric
R31: R_Shunt; R_Shunt_Vishay_WSK2512_6332Metric_T2.66mm
TP7: TestPoint; TestPoint_Pad_D2.0mm
U10: LM76005RNPR; QFN50P600X400X80-31N; PARTREV A; DigiKey_Part_Number 296-LM76005RNPRCT-ND
U11: INA228; TSSOP-10_3x3mm_P0.5mm

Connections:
+5V@4A: R30.1, R31.4, TP7.1 (1_1); also elsewhere on the board
+BATT: C26.1, C27.1, U10.18 (EN), U10.20 (PVIN), U10.21 (PVIN), U10.22 (PVIN); also elsewhere on the board
/5V@4A/+3.3V: C32.2, U11.1 (A1), U11.6 (VS)
/5V@4A/SCL: U11.5 (SCL)
/5V@4A/SDA: U11.4 (SDA)
GND: C26.2, C27.2, C28.2, C30.2, C31.2, C32.1, D14.1 (K), R29.2, U10.7 (NC), U10.9 (BIAS), U10.13 (AGND), U10.14 (AGND), U10.15 (AGND), U10.17 (SYNC/MODE), U10.19 (NC), U10.23 (NC), U10.24 (PGND), U10.25 (PGND), U10.26 (PGND), U10.27 (NC), U10.28 (NC), U10.29 (NC), U10.30 (NC), U10.31 (EP), U11.2 (A0), U11.7 (GND); also elsewhere on the board
unnamed: C29.1, L2.1, U10.1 (SW), U10.2 (SW), U10.3 (SW), U10.4 (SW), U10.5 (SW)
unnamed: C30.1, C31.1, F2.2, L2.2, R27.2, R28.1
unnamed: D14.2 (A), R30.2
unnamed: C29.2, U10.6 (BOOT)
unnamed: R28.2, R29.1, U10.12 (FB)
unnamed: R27.1, U10.16 (PGOOD)
unnamed: C28.1, U10.8 (VCC)
unnamed: F2.1, R31.1, U11.8 (Vbus)

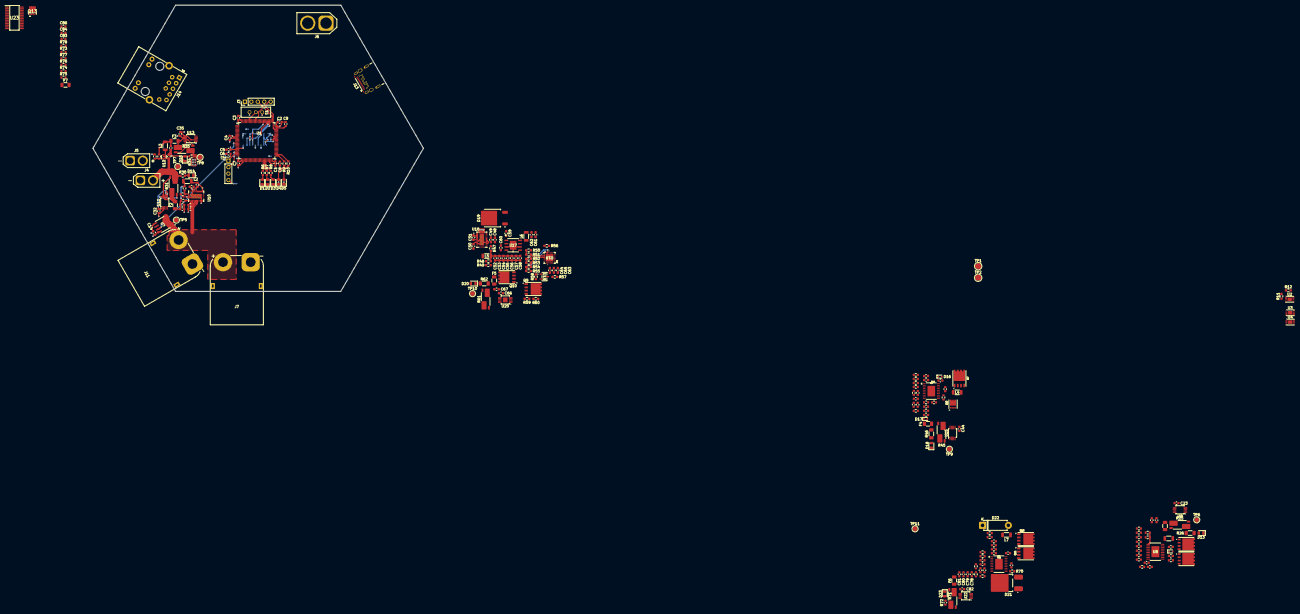
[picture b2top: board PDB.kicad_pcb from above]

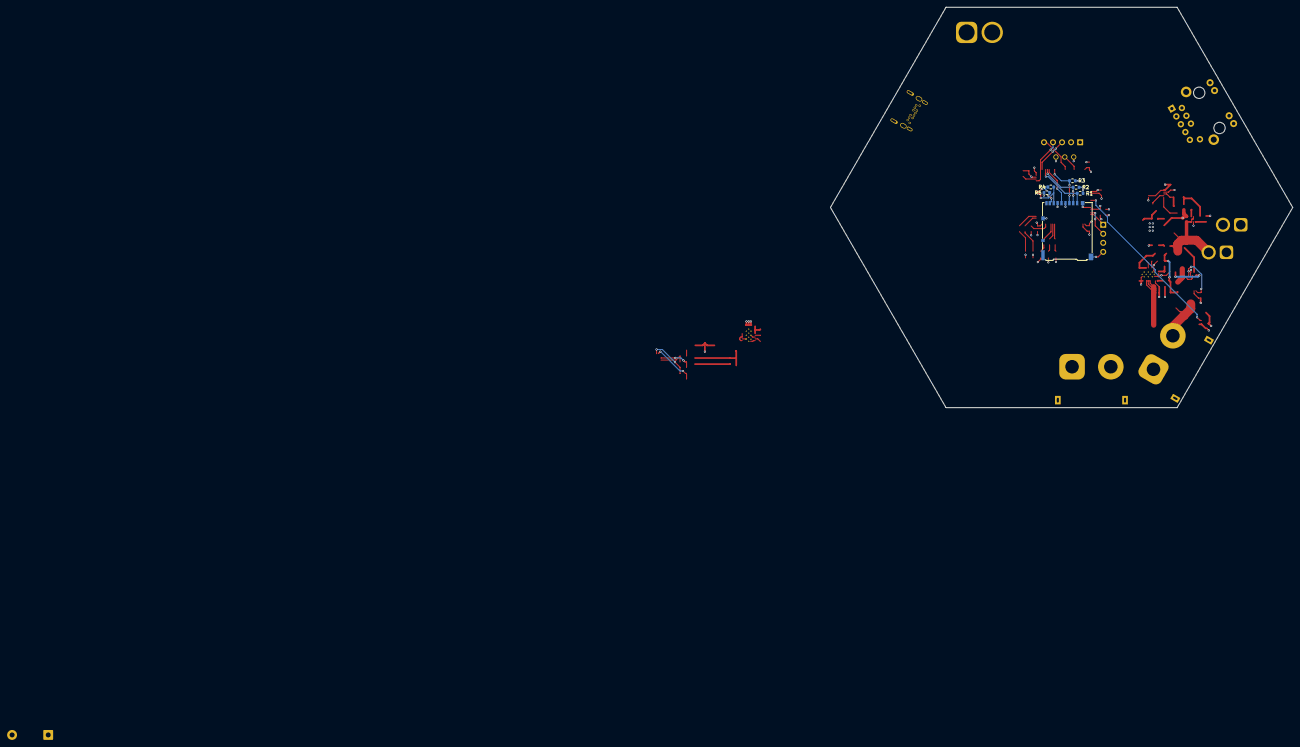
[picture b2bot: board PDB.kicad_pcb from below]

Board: 6 copper layers, 130.0 x 112.6 mm, 236 parts (6 on the bottom side), 145 nets.
